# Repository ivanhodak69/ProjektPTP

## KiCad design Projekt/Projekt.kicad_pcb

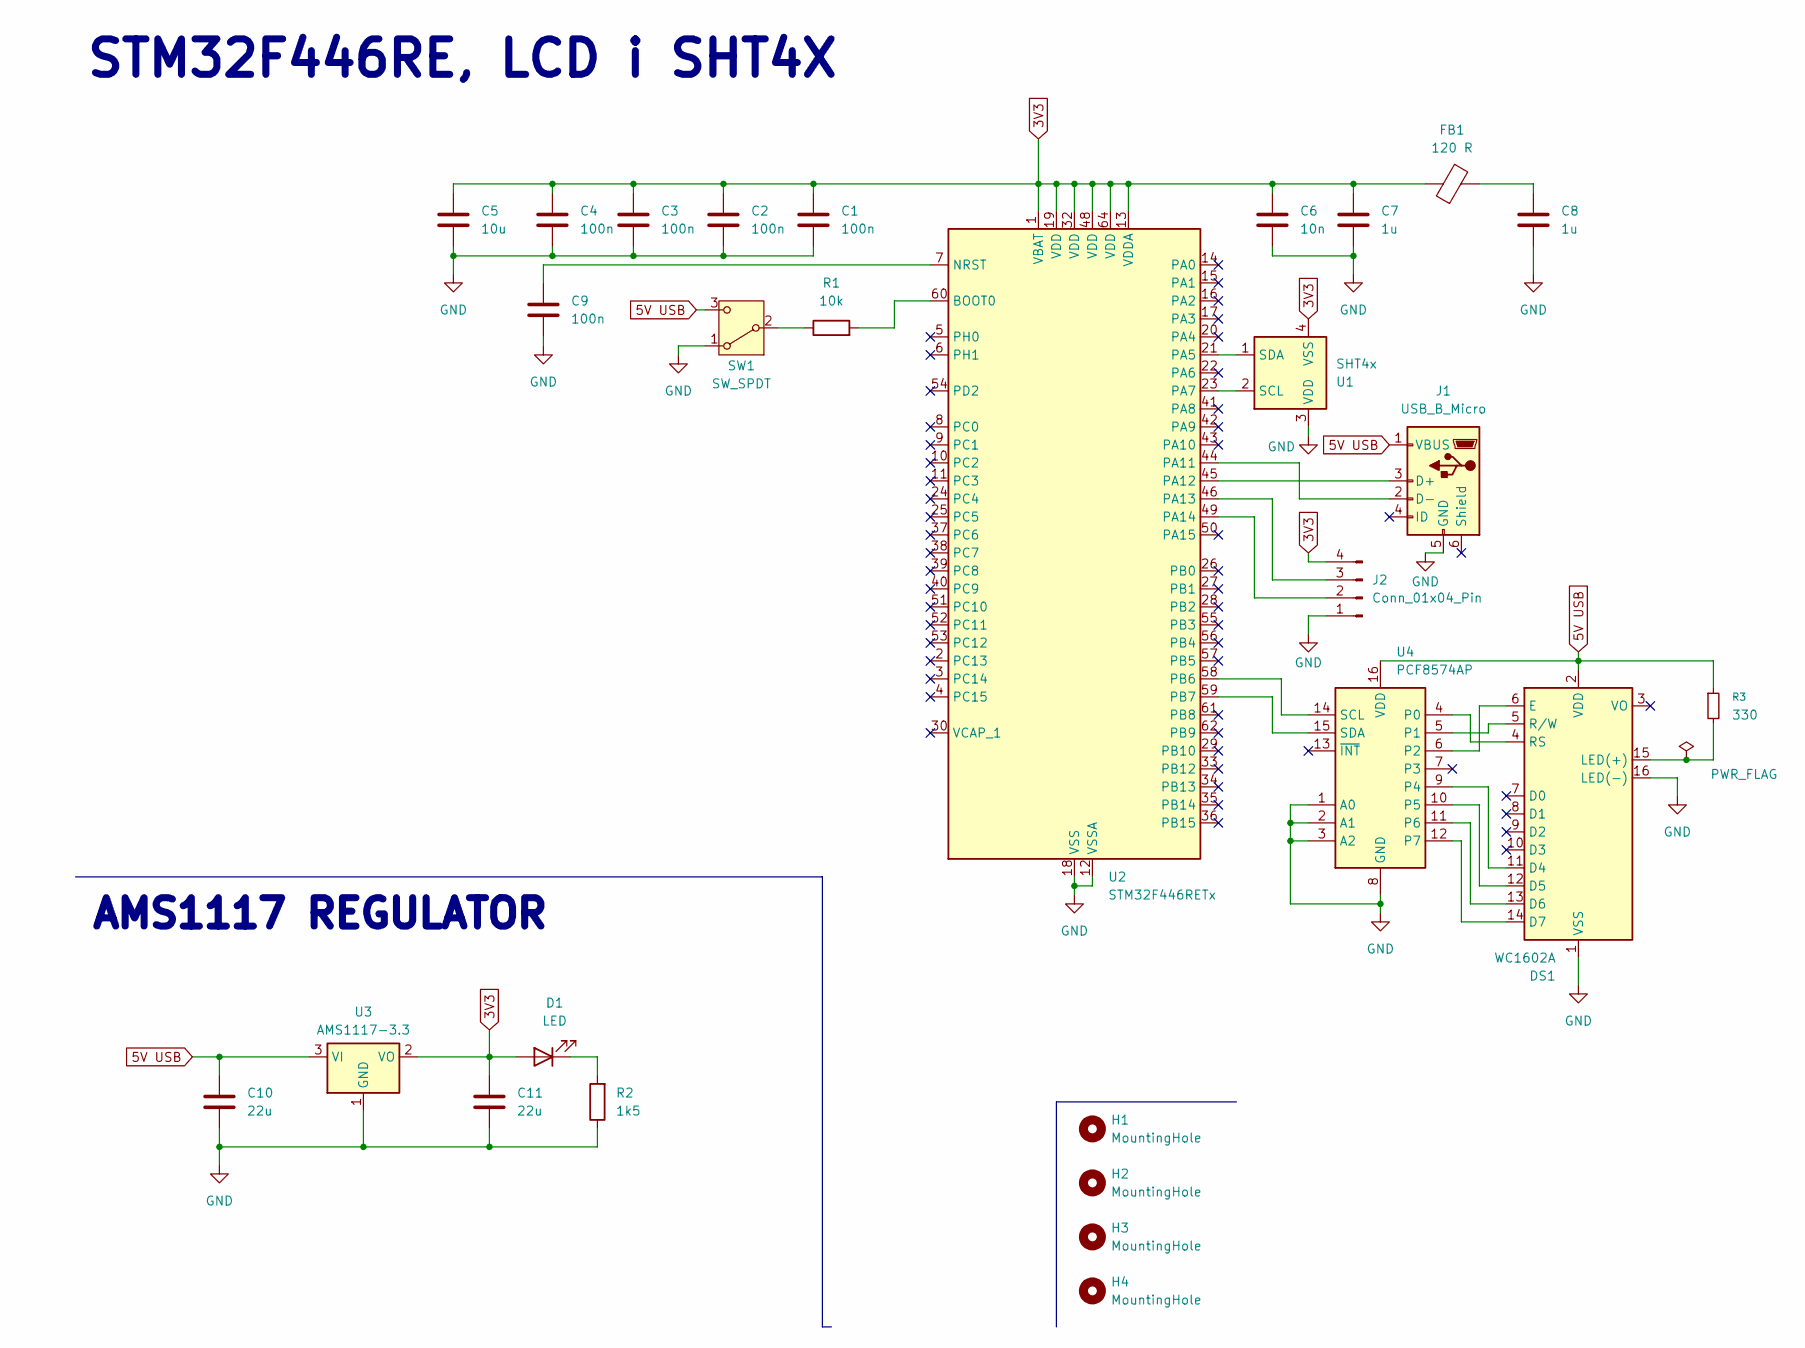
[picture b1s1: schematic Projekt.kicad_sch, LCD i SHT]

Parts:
C1, C2, C3, C4, C9: 100n; C_0402_1005Metric
C5: 10u; C_0402_1005Metric
C6: 10n; C_0402_1005Metric
C7, C8: 1u; C_0402_1005Metric
C10, C11: 22u; C_0805_2012Metric
D1: LED; LED_0603_1608Metric
DS1: WC1602A
FB1: 120 R; L_0603_1608Metric
H1, H2, H3, H4: MountingHole; MountingHole_2mm
J1: USB_B_Micro; USB_Micro-B_Wuerth_629105150521
J2: Conn_01x04_Pin; PinHeader_1x04_P2.54mm_Vertical
R1: 10k; R_0402_1005Metric
R2: 1k5; R_0402_1005Metric
R3: 330; R_0402_1005Metric; Manufacturer part number 1206S4F2001T5E
SW1: SW_SPDT; SW_E-Switch_EG1224_SPDT_Angled
U1: SHT4x; Sensirion_DFN-4_1.5x1.5mm_P0.8mm_SHT4x_NoCentralPad
U2: STM32F446RETx; LQFP-64_10x10mm_P0.5mm
U3: AMS1117-3.3; SOT-223-3_TabPin2
U4: PCF8574AP; DIP-16_W7.62mm

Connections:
3V3: C1.1, C2.1, C3.1, C4.1, C5.1, C6.1, C7.1, C11.1, D1.2 (A), FB1.1, J2.4, U1.4 (VSS), U2.1 (VBAT), U2.13 (VDDA), U2.19 (VDD), U2.32 (VDD), U2.48 (VDD), U2.64 (VDD), U3.2 (VO)
5V USB: C10.1, DS1.2 (VDD), J1.1 (VBUS), R3.1, SW1.3 (C), U3.3 (VI), U4.16 (VDD)
GND: C1.2, C2.2, C3.2, C4.2, C5.2, C6.2, C7.2, C8.2, C9.2, C10.2, C11.2, DS1.1 (VSS), DS1.16 (LED(-)), J1.5 (GND), J2.1, R2.1, SW1.1 (A), U1.3 (VDD), U2.12 (VSSA), U2.18 (VSS), U2.31 (VSS), U2.47 (VSS), U2.63 (VSS), U3.1 (GND), U4.1 (A0), U4.2 (A1), U4.3 (A2), U4.8 (GND)
unnamed: C8.1, FB1.2
unnamed: D1.1 (K), R2.2
unnamed: DS1.11 (D4), U4.9 (P4)
unnamed: DS1.12 (D5), U4.10 (P5)
unnamed: DS1.13 (D6), U4.11 (P6)
unnamed: DS1.14 (D7), U4.12 (P7)
unnamed: DS1.6 (E), U4.6 (P2)
unnamed: DS1.15 (LED(+)), R3.2
unnamed: DS1.4 (RS), U4.4 (P0)
unnamed: DS1.5 (R/W), U4.5 (P1)
unnamed: J1.3 (D+), U2.45 (PA12)
unnamed: J1.2 (D-), U2.44 (PA11)
unnamed: J2.2, U2.49 (PA14)
unnamed: J2.3, U2.46 (PA13)
unnamed: R1.1, SW1.2 (B)
unnamed: U1.2 (SCL), U2.23 (PA7)
unnamed: U1.1 (SDA), U2.21 (PA5)
unnamed: R1.2, U2.60 (BOOT0)
unnamed: C9.1, U2.7 (NRST)
unnamed: U2.58 (PB6), U4.14 (SCL)
unnamed: U2.59 (PB7), U4.15 (SDA)

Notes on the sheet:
AMS1117 REGULATOR
STM32F446RE, LCD i SHT4X

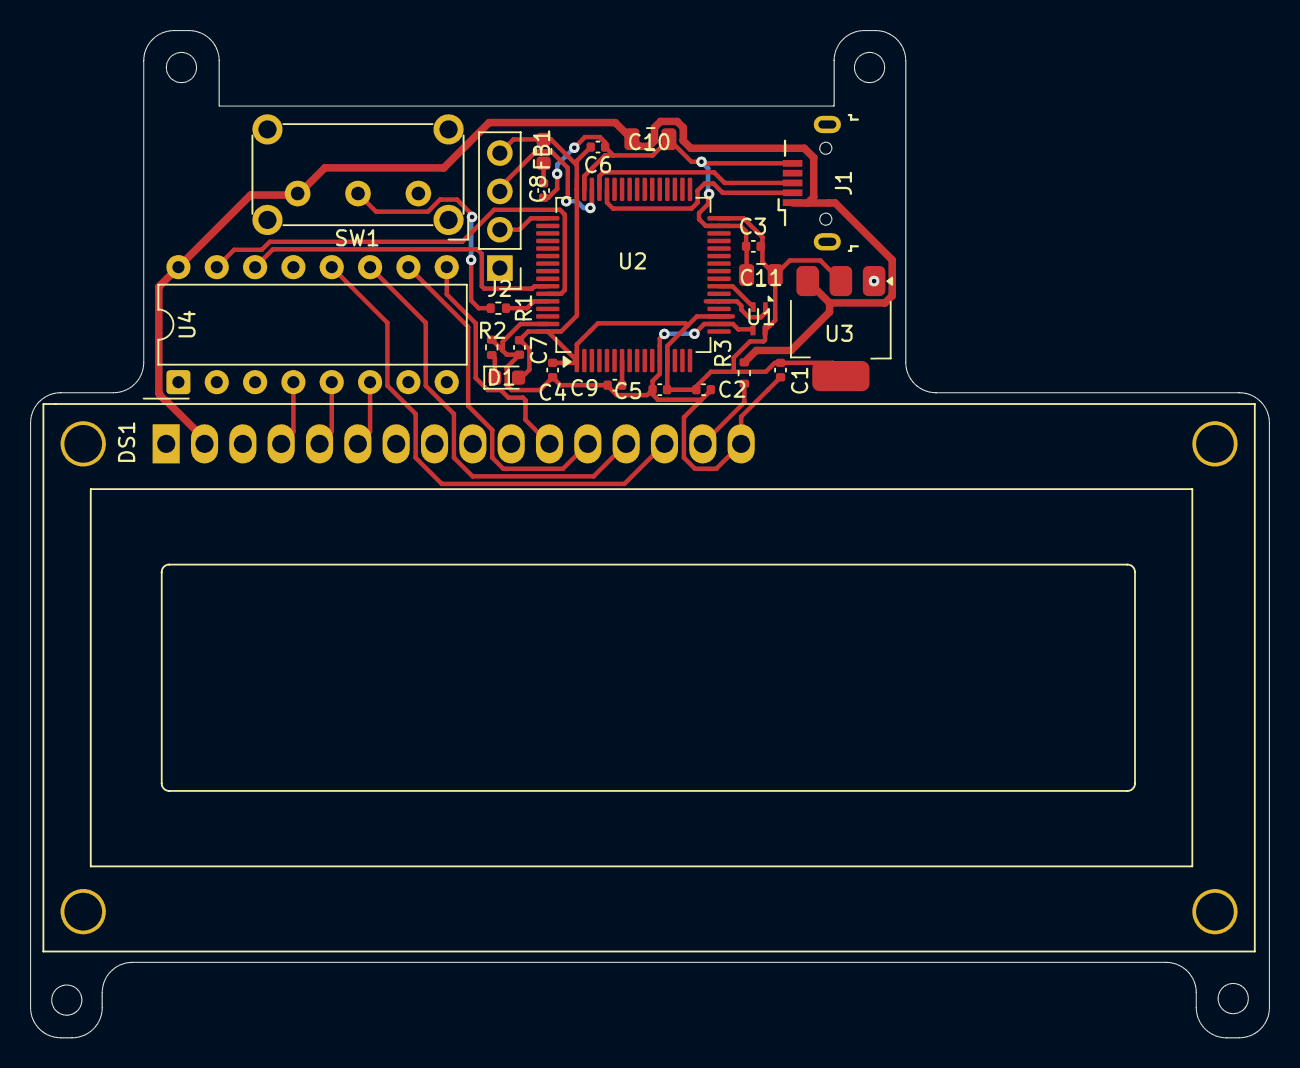
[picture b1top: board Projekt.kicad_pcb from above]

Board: 2 copper layers, 82.1 x 66.8 mm, 28 parts (0 on the bottom side), 24 nets.

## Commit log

2026-06-20 Final
